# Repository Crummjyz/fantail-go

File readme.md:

# Fantail Go

Throughout 2019, we, a group of students, worked to build an electric go-kart from the ground up. Across the entire vehicle _everything_ was controlled digitally via a pair of Raspberry Pi’s — giving us detailed control over performance, and _lots_ of diagnostics data.

**This repository is not a prepared do-it-yourself project.** Instead, we hope that it might provide some appreciated insight into someone else’s approaches to common problems, for your own work.

The structural and mechanical designs will remain private.

## Repository Structure
#### [vehicle](https://github.com/Crummjyz/fantail-go/tree/main/vehicle)
The code running on each of the onboard Raspberry Pi’s, providing control of the vehicle and data transmission/processing.
_Note — the programs in the ‘tests’ folders are not software tests, but small, isolated scripts to allow manual operation of some hardware components. _

#### [dash](https://github.com/Crummjyz/fantail-go/tree/main/dash)
A Flutter app to display realtime data to the driver.

#### [board](https://github.com/Crummjyz/fantail-go/tree/main/board)
The EAGLE files for our custom PCB/breakout-board.

---- 
_This repository was originally at [https://github.com/Fantail-Dev/fantail-go](https://github.com/Fantail-Dev/fantail-go). It has been migrated here for easier oversight._

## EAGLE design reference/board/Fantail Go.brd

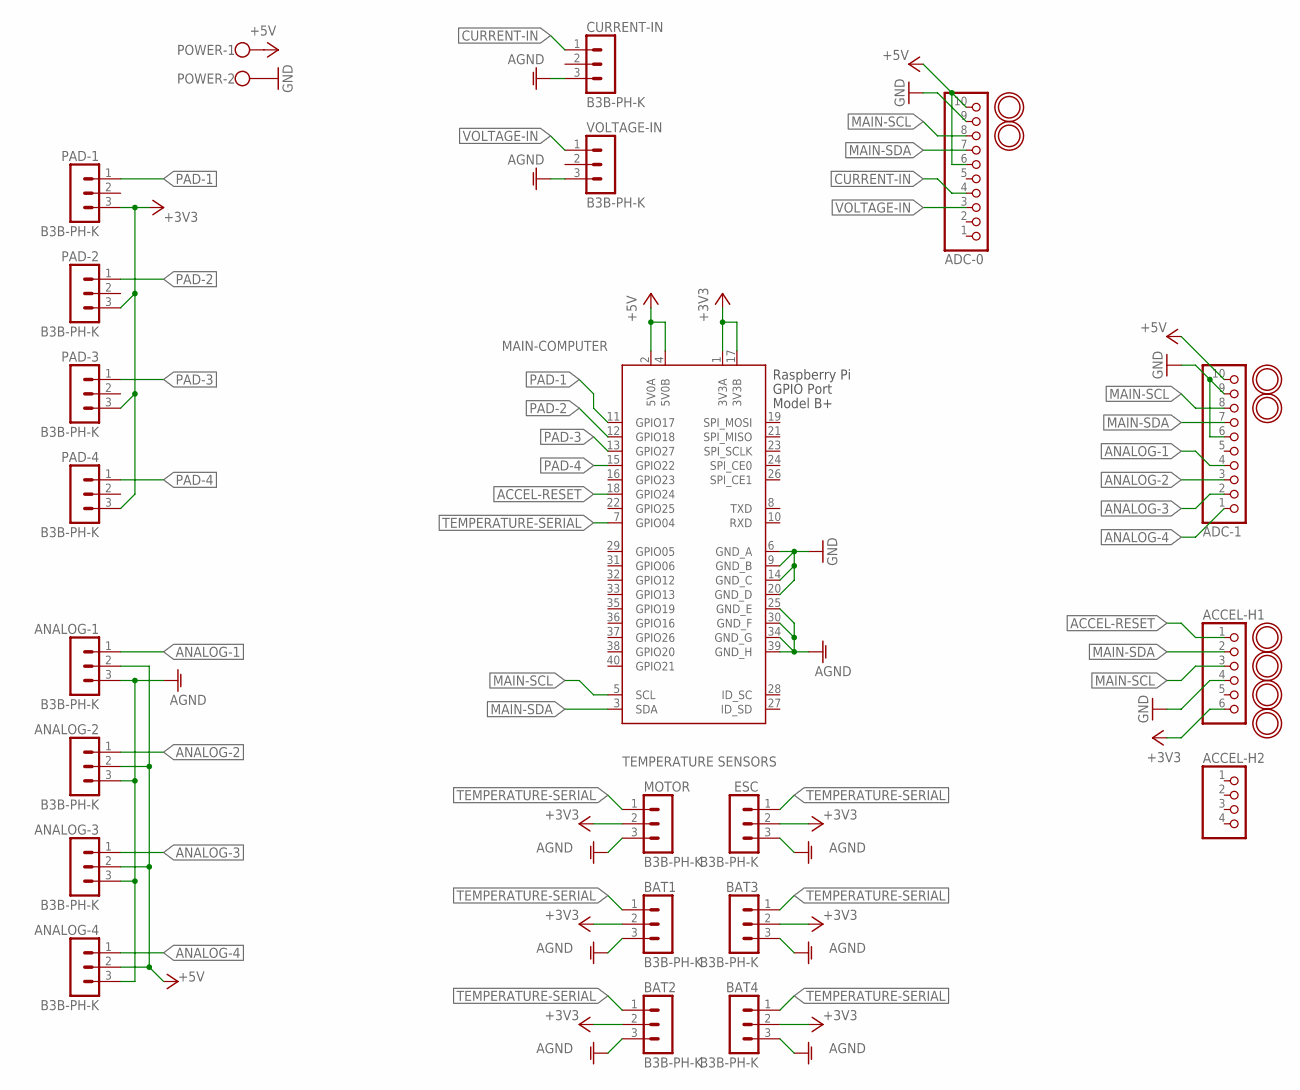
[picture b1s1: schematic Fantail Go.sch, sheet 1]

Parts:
ACCEL-H1: HEADER-1X670MIL; 1X06_ROUND_70
ACCEL-H2: HEADER-1X4ROUND; 1X04_ROUND
ADC-0, ADC-1: HEADER-1X1070MIL; 1X10_ROUND70
ANALOG-1, ANALOG-2, ANALOG-3, ANALOG-4: B3B-PH-K
BAT1, BAT2, BAT3, BAT4: B3B-PH-K
CURRENT-IN: B3B-PH-K
ESC: B3B-PH-K
MOTOR: B3B-PH-K
PAD-1, PAD-2, PAD-3, PAD-4: B3B-PH-K
POWER: W237-102
U$5, U$15, U$16, U$18, U$19, U$20, U$21, U$22: MOUNTINGHOLE2.5; MOUNTINGHOLE_2.5_PLATED
VOLTAGE-IN: B3B-PH-K
X1: RASPI_BOARD_B+#_F; RASPI_BOARD_B+_FULL

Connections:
+3V3: ACCEL-H1.6, BAT1.2, BAT2.2, BAT3.2, BAT4.2, ESC.2, MOTOR.2, PAD-1.3, PAD-2.3, PAD-3.3, PAD-4.3, X1.1 (3V3A), X1.17 (3V3B)
+5V: ADC-0.6, ADC-0.10, ADC-1.10, ANALOG-1.2, ANALOG-2.2, ANALOG-3.2, ANALOG-4.2, POWER.1, X1.2 (5V0A), X1.4 (5V0B); also elsewhere on the board
ACCEL-RESET: ACCEL-H1.1, X1.18 (GPIO24)
AGND: ANALOG-1.3, ANALOG-2.3, ANALOG-3.3, ANALOG-4.3, BAT1.3, BAT2.3, BAT3.3, BAT4.3, CURRENT-IN.3, ESC.3, MOTOR.3, VOLTAGE-IN.3, X1.25 (GND_E), X1.30 (GND_F), X1.34 (GND_G), X1.39 (GND_H)
ANALOG-1: ADC-1.4, ANALOG-1.1
ANALOG-2: ADC-1.3, ANALOG-2.1
ANALOG-3: ADC-1.2, ANALOG-3.1
ANALOG-4: ADC-1.1, ANALOG-4.1
CURRENT-IN: ADC-0.4, CURRENT-IN.1
GND: ACCEL-H1.4, ADC-0.9, ADC-1.6, ADC-1.9, POWER.2, X1.6 (GND_A), X1.9 (GND_B), X1.14 (GND_C), X1.20 (GND_D); also elsewhere on the board
MAIN-SCL: ACCEL-H1.3, ADC-0.8, ADC-1.8, X1.5 (SCL)
MAIN-SDA: ACCEL-H1.2, ADC-0.7, ADC-1.7, X1.3 (SDA)
PAD-1: PAD-1.1, X1.11 (GPIO17)
PAD-2: PAD-2.1, X1.12 (GPIO18)
PAD-3: PAD-3.1, X1.13 (GPIO27)
PAD-4: PAD-4.1, X1.15 (GPIO22)
TEMPERATURE-SERIAL: BAT1.1, BAT2.1, BAT3.1, BAT4.1, ESC.1, MOTOR.1, X1.7 (GPIO04)
VOLTAGE-IN: ADC-0.3, VOLTAGE-IN.1

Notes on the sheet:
TEMPERATURE SENSORS
MAIN-COMPUTER

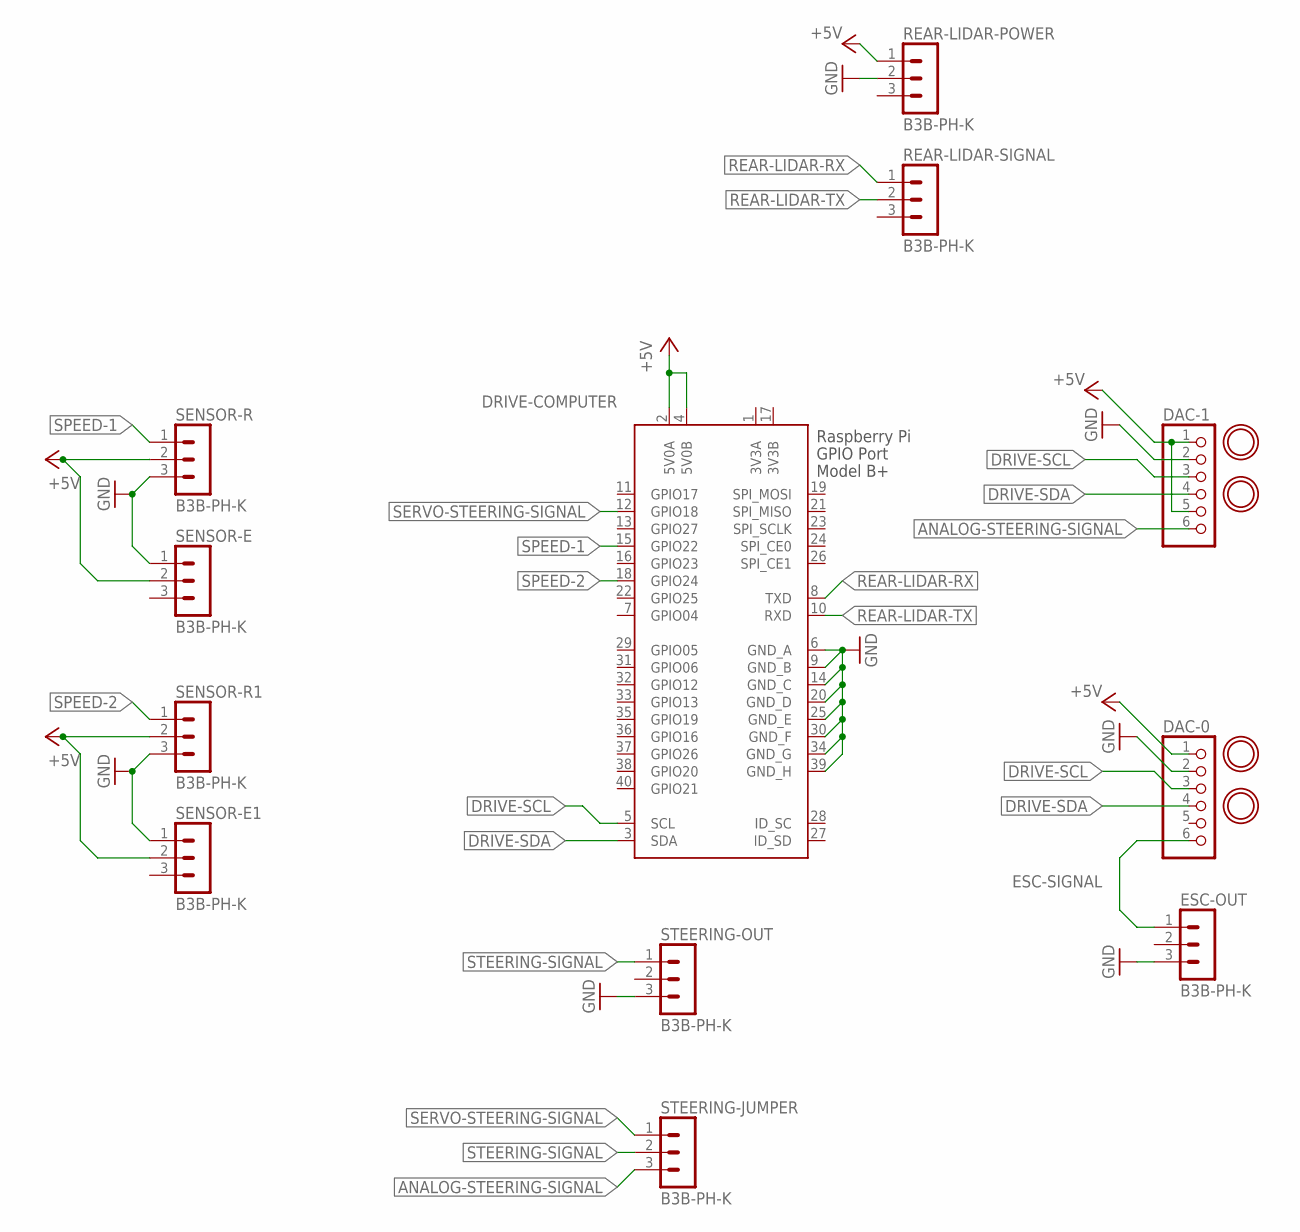
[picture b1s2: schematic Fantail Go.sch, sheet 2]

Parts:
DAC-0, DAC-1: HEADER-1X670MIL; 1X06_ROUND_70
ESC-OUT: B3B-PH-K
REAR-LIDAR-POWER: B3B-PH-K
REAR-LIDAR-SIGNAL: B3B-PH-K
SENSOR-E, SENSOR-E1: B3B-PH-K
SENSOR-R, SENSOR-R1: B3B-PH-K
STEERING-JUMPER: B3B-PH-K
STEERING-OUT: B3B-PH-K
U$7, U$8, U$11, U$12: MOUNTINGHOLE2.5; MOUNTINGHOLE_2.5_PLATED
X2: RASPI_BOARD_B+#_F; RASPI_BOARD_B+_FULL

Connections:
3V3A: X2.1 (3V3A)
3V3B: X2.17 (3V3B)
+5V: DAC-0.1, DAC-1.1, DAC-1.5, REAR-LIDAR-POWER.1, SENSOR-E.2, SENSOR-E1.2, SENSOR-R.2, SENSOR-R1.2, X2.2 (5V0A), X2.4 (5V0B); also elsewhere on the board
ANALOG-STEERING-SIGNAL: DAC-1.6, STEERING-JUMPER.3
DRIVE-SCL: DAC-0.3, DAC-1.3, X2.5 (SCL)
DRIVE-SDA: DAC-0.4, DAC-1.4, X2.3 (SDA)
ESC-SIGNAL: DAC-0.6, ESC-OUT.1
GND: DAC-0.2, DAC-1.2, ESC-OUT.3, REAR-LIDAR-POWER.2, SENSOR-E.1, SENSOR-E1.1, SENSOR-R.3, SENSOR-R1.3, STEERING-OUT.3, X2.6 (GND_A), X2.9 (GND_B), X2.14 (GND_C), X2.20 (GND_D), X2.25 (GND_E), X2.30 (GND_F), X2.34 (GND_G), X2.39 (GND_H); also elsewhere on the board
REAR-LIDAR-RX: REAR-LIDAR-SIGNAL.1, X2.8 (TXD)
REAR-LIDAR-TX: REAR-LIDAR-SIGNAL.2, X2.10 (RXD)
SERVO-STEERING-SIGNAL: STEERING-JUMPER.1, X2.12 (GPIO18)
SPEED-1: SENSOR-R.1, X2.15 (GPIO22)
SPEED-2: SENSOR-R1.1, X2.18 (GPIO24)
STEERING-SIGNAL: STEERING-JUMPER.2, STEERING-OUT.1

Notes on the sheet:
DRIVE-COMPUTER

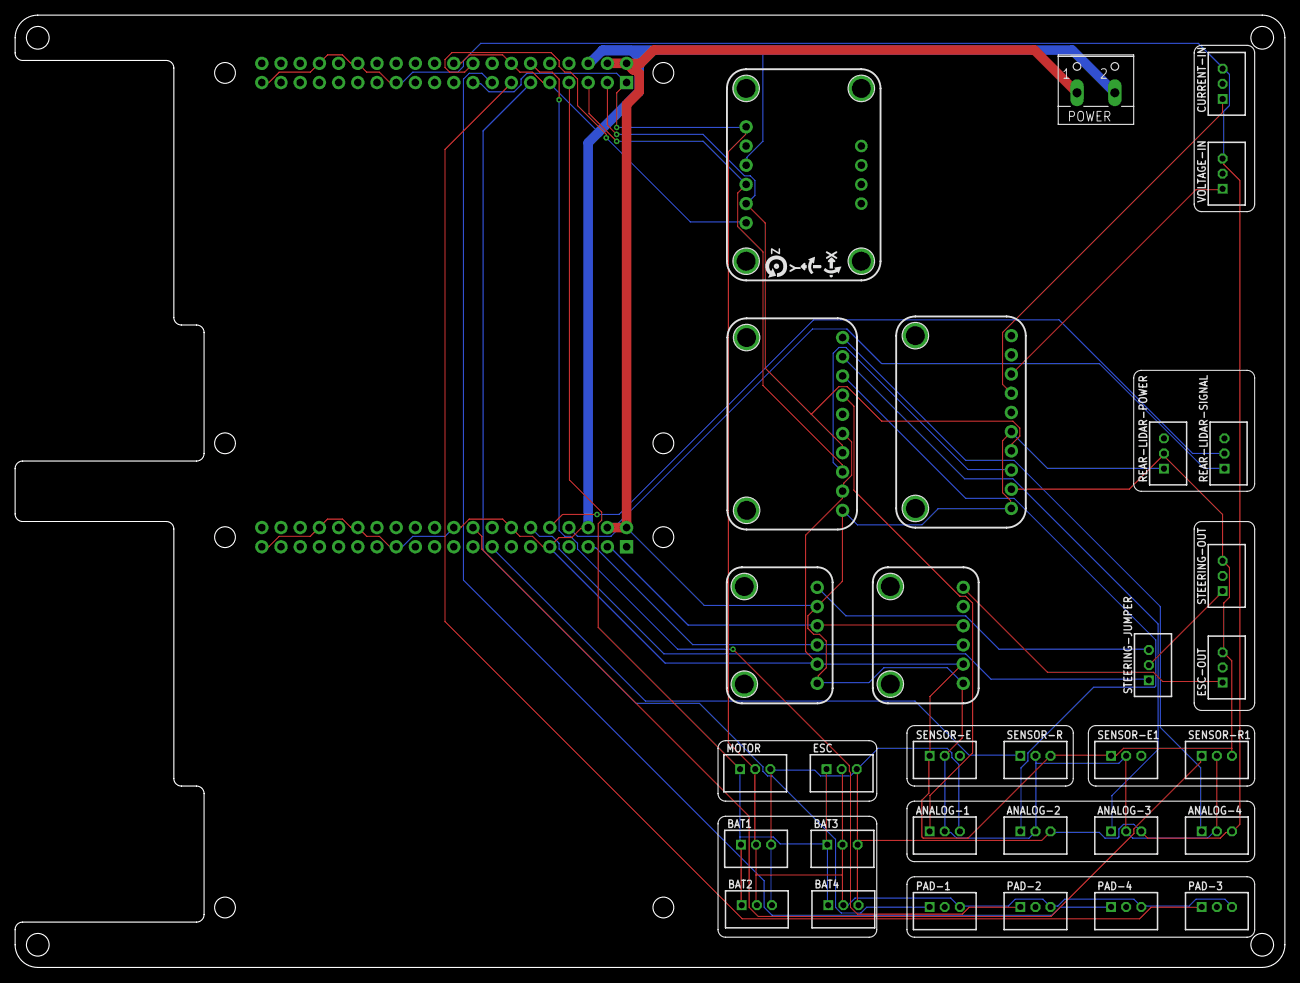
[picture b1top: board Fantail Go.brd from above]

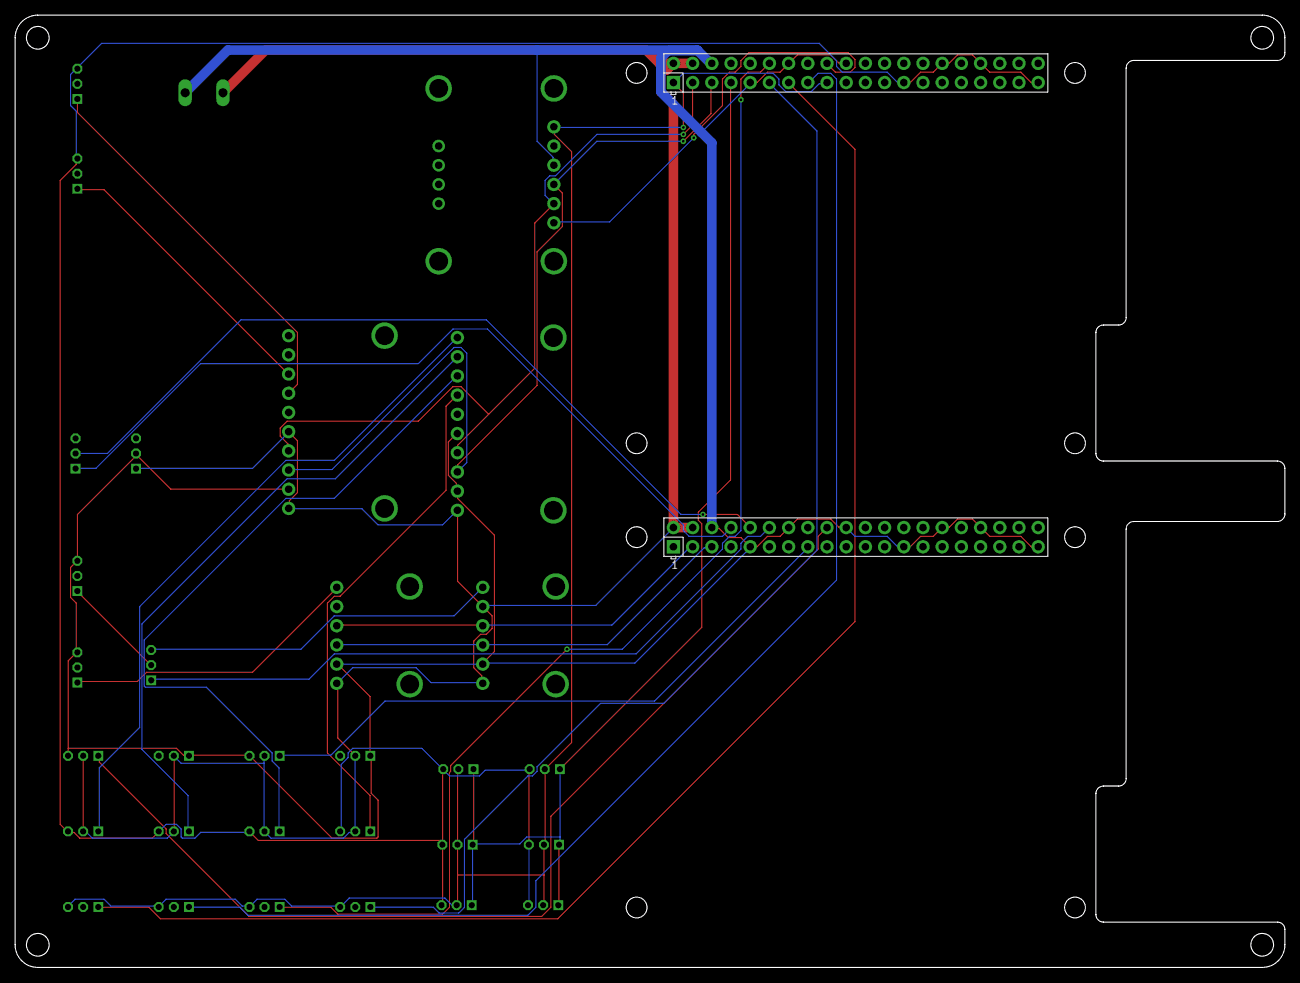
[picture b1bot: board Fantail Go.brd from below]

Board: 2 copper layers, 168.0 x 126.0 mm, 49 parts (2 on the bottom side), 28 nets.

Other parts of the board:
U$35: SYMBOL_GYRO_CCLOCKWISE
U$36: SYMBOL_GYRO_CLOCKWISE
U$37: SYMBOL_GYRO_Z

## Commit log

2019-11-20 Add .gitignore
2019-11-20 Add PCB files
2019-11-20 Add vehicle code
2019-11-20 Add dash
2019-11-20 Add readme.md
2019-11-20 Add main.dart
2021-11-20 Update README.md ahead of archival

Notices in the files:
parts and their libraries:
con-jst-ph: Copyright (C) 2016, Bob Starr
